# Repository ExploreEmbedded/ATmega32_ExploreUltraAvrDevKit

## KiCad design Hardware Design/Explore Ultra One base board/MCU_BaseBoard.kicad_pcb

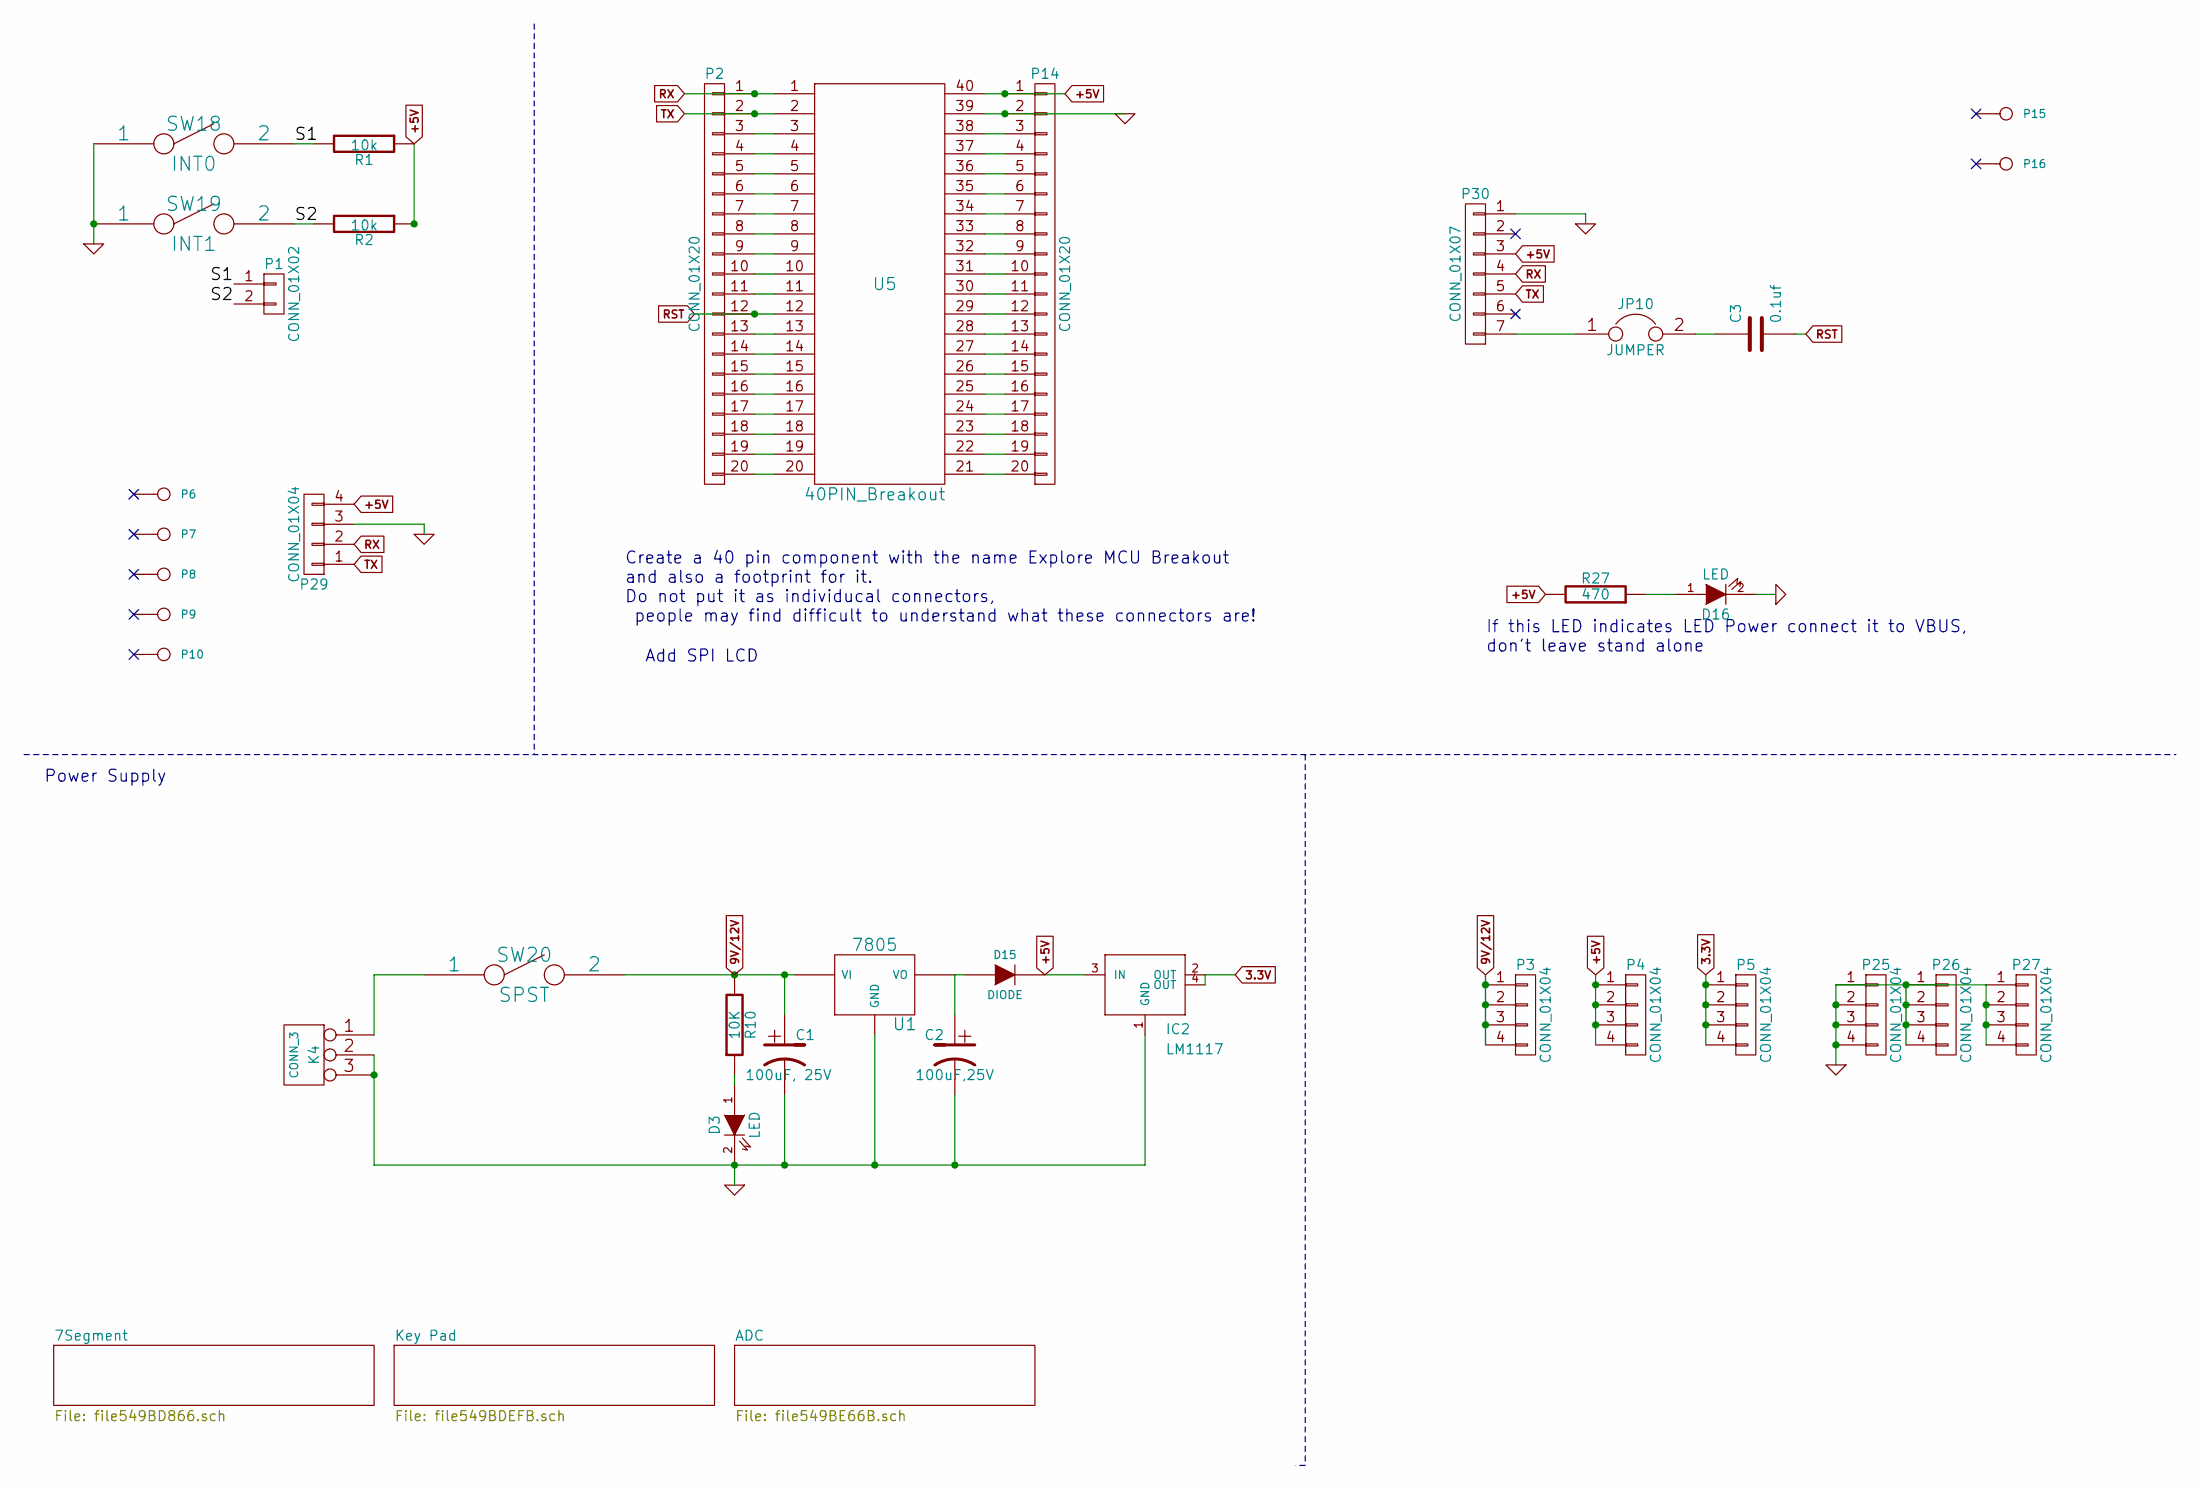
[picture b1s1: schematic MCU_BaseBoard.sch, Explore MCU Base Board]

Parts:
C1: 100uF, 25V
C2: 100uF,25V
C3: 0.1uf
D3, D16: LED
D15: DIODE
IC2: LM1117
JP10: JUMPER
K4: CONN_3
P1: CONN_01X02
P2, P14: CONN_01X20
P3, P4, P5, P25, P26, P27, P29: CONN_01X04
P6, P7, P8, P9, P10, P15, P16: CONN_1
P30: CONN_01X07
R1, R2: 10k
R10: 10K
R27: 470
SW18: INT0
SW19: INT1
SW20: SPST
U1: 7805
U5: 40PIN_Breakout

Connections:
3.3V: IC2.2 (OUT), IC2.4 (OUT), P5.1, P5.2, P5.3, P5.4; also elsewhere on the board
9V/12V: C1.1, P3.1, P3.2, P3.3, P3.4, R10.2, SW20.2, U1.VI; also elsewhere on the board
+5V: D15.2 (K), IC2.3 (IN), P4.1, P4.2, P4.3, P4.4, P14.1, P29.4, P30.3, R1.1, R2.1, R27.2, U5.40; also elsewhere on the board
/S1: P1.1, R1.2, SW18.2
/S2: P1.2, R2.2, SW19.2
GND: C1.2, C2.2, D3.2 (K), D16.2 (K), IC2.1 (GND), K4.2 (PM), K4.3, P14.2, P25.1, P25.2, P25.3, P25.4, P26.1, P26.2, P26.3, P26.4, P27.1, P27.2, P27.3, P27.4, P29.3, P30.1, SW18.1, SW19.1, U1.GND, U5.39; also elsewhere on the board
unnamed: C2.1, D15.1 (A), U1.VO
unnamed: C3.1, JP10.2
unnamed: D3.1 (A), R10.1
unnamed: D16.1 (A), R27.1
unnamed: JP10.1, P30.7
unnamed: K4.1, SW20.1
unnamed: P2.3, U5.3
unnamed: P2.4, U5.4
unnamed: P2.5, U5.5
unnamed: P2.6, U5.6
unnamed: P2.7, U5.7
unnamed: P2.8, U5.8
unnamed: P2.9, U5.9
unnamed: P2.10, U5.10
unnamed: P2.11, U5.11
unnamed: P2.13, U5.13
unnamed: P2.14, U5.14
unnamed: P2.15, U5.15
unnamed: P2.16, U5.16
unnamed: P2.17, U5.17
unnamed: P2.18, U5.18
unnamed: P2.19, U5.19
unnamed: P2.20, U5.20
unnamed: P14.3, U5.38
unnamed: P14.4, U5.37
unnamed: P14.5, U5.36
unnamed: P14.6, U5.35
unnamed: P14.7, U5.34
unnamed: P14.8, U5.33
unnamed: P14.9, U5.32
unnamed: P14.10, U5.31
unnamed: P14.11, U5.30
unnamed: P14.12, U5.29
unnamed: P14.13, U5.28
unnamed: P14.14, U5.27
unnamed: P14.15, U5.26
unnamed: P14.16, U5.25
unnamed: P14.17, U5.24
unnamed: P14.18, U5.23
unnamed: P14.19, U5.22
unnamed: P14.20, U5.21
RST: C3.2, P2.12, U5.12
RX: P2.1, P29.2, P30.4, U5.1
TX: P2.2, P29.1, P30.5, U5.2

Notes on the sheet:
Power Supply
Create a 40 pin component with the name Explore MCU Breakout and also a footprint for it. Do not put it as individucal connectors, people may find difficult to understand what these connectors are!
If this LED indicates LED Power connect it to VBUS, don't leave stand alone
Add SPI LCD

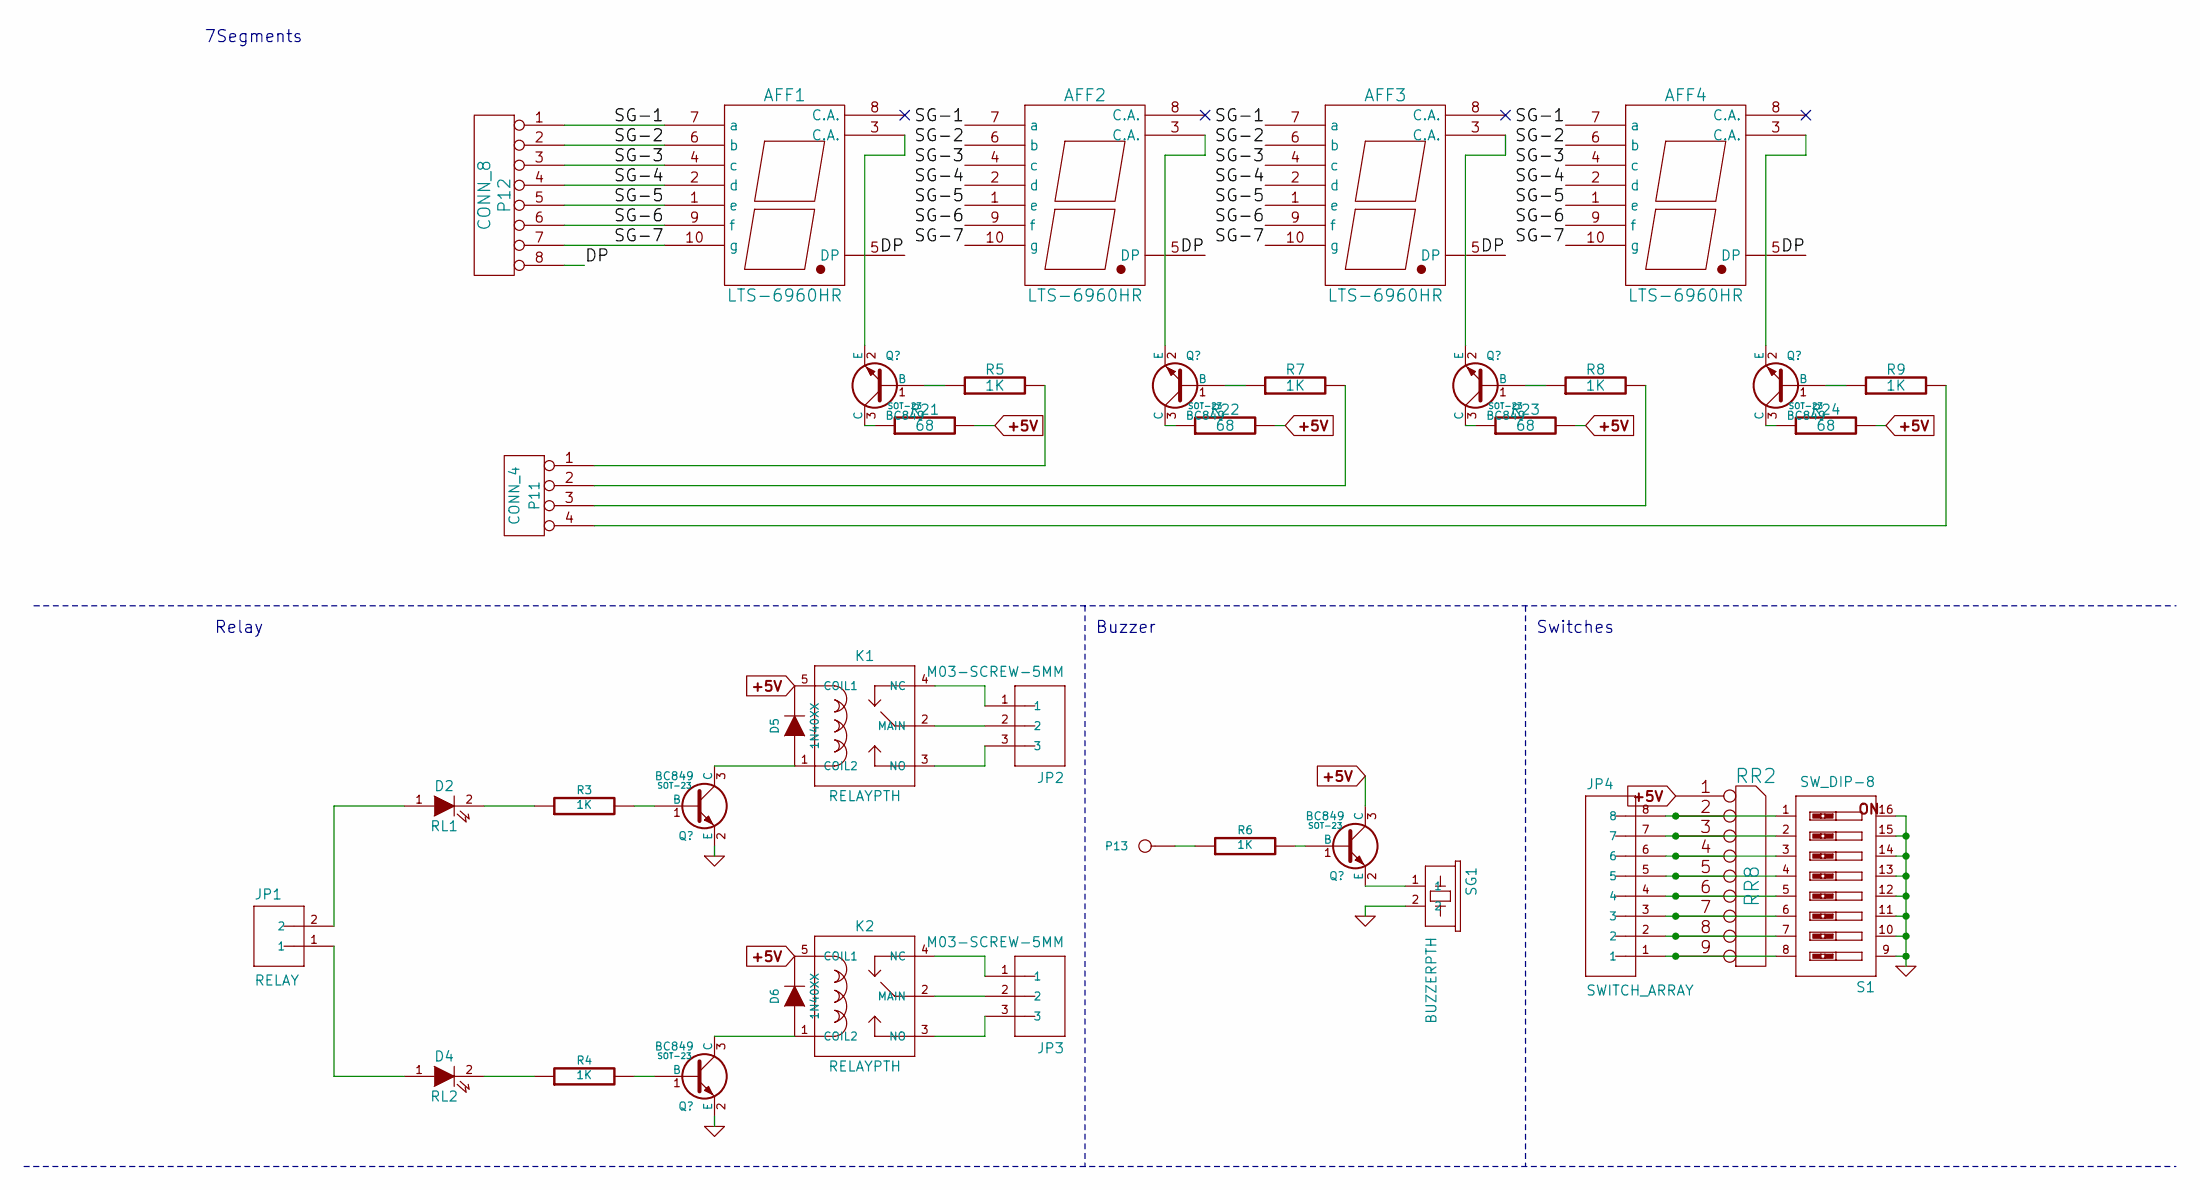
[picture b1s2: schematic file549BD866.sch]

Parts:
AFF1, AFF2, AFF3, AFF4: LTS-6960HR
D2: RL1
D4: RL2
D5, D6: 1N40XX
JP1: RELAY; SparkFun-JST-2-PTH-NS
JP2, JP3: M03-SCREW-5MM; SparkFun-SCREWTERMINAL-5MM-3
JP4: SWITCH_ARRAY; SparkFun-1X08_LOCK
K1, K2: RELAYPTH
P11: CONN_4
P12: CONN_8
P13: CONN_1
R3, R4, R6: 1K
R5, R7, R8, R9: 1K
R21, R22, R23, R24: 68
RR2: RR8
S1: SW_DIP-8; SparkFun-DIPSWITCH-08
SG1: BUZZERPTH; SparkFun-BUZZER-12MM

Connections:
+5V: D5.2 (K), D6.2 (K), K1.5 (COIL1), K2.5 (COIL1), R21.2, R22.2, R23.2, R24.2, RR2.1 (COM); also elsewhere on the board
/7Segment/DP: AFF1.5 (DP), AFF2.5 (DP), AFF3.5 (DP), AFF4.5 (DP), P12.8
/7Segment/SG-1: AFF1.7 (a), AFF2.7 (a), AFF3.7 (a), AFF4.7 (a), P12.1
/7Segment/SG-2: AFF1.6 (b), AFF2.6 (b), AFF3.6 (b), AFF4.6 (b), P12.2
/7Segment/SG-3: AFF1.4 (c), AFF2.4 (c), AFF3.4 (c), AFF4.4 (c), P12.3
/7Segment/SG-4: AFF1.2 (d), AFF2.2 (d), AFF3.2 (d), AFF4.2 (d), P12.4
/7Segment/SG-5: AFF1.1 (e), AFF2.1 (e), AFF3.1 (e), AFF4.1 (e), P12.5
/7Segment/SG-6: AFF1.9 (f), AFF2.9 (f), AFF3.9 (f), AFF4.9 (f), P12.6
/7Segment/SG-7: AFF1.10 (g), AFF2.10 (g), AFF3.10 (g), AFF4.10 (g), P12.7
GND: S1.9, S1.10, S1.11, S1.12, S1.13, S1.14, S1.15, S1.16, SG1.2; also elsewhere on the board
unnamed 46: AFF1.3 (C.A.); also elsewhere on the board
unnamed 48: AFF2.3 (C.A.); also elsewhere on the board
unnamed 50: AFF3.3 (C.A.); also elsewhere on the board
unnamed 52: AFF4.3 (C.A.); also elsewhere on the board
unnamed: D2.1 (A), JP1.2
unnamed: D2.2 (K), R3.1
unnamed: D4.1 (A), JP1.1
unnamed: D4.2 (K), R4.1
unnamed 61: D5.1 (A), K1.1 (COIL2); also elsewhere on the board
unnamed 62: D6.1 (A), K2.1 (COIL2); also elsewhere on the board
unnamed: JP2.1, K1.4 (NC)
unnamed: JP2.2, K1.2 (MAIN)
unnamed: JP2.3, K1.3 (NO)
unnamed: JP3.1, K2.4 (NC)
unnamed: JP3.2, K2.2 (MAIN)
unnamed: JP3.3, K2.3 (NO)
unnamed: JP4.1, RR2.9, S1.8
unnamed: JP4.2, RR2.8, S1.7
unnamed: JP4.3, RR2.7, S1.6
unnamed: JP4.4, RR2.6, S1.5
unnamed: JP4.5, RR2.5, S1.4
unnamed: JP4.6, RR2.4, S1.3
unnamed: JP4.7, RR2.3, S1.2
unnamed: JP4.8, RR2.2, S1.1
unnamed: P11.1, R5.2
unnamed: P11.2, R7.2
unnamed: P11.3, R8.2
unnamed: P11.4, R9.2
unnamed: P13.1, R6.1
unnamed 157: R3.2; also elsewhere on the board
unnamed 158: R4.2; also elsewhere on the board
unnamed 159: R5.1; also elsewhere on the board
unnamed 160: R21.1; also elsewhere on the board
unnamed 161: R7.1; also elsewhere on the board
unnamed 162: R22.1; also elsewhere on the board
unnamed 163: R6.2; also elsewhere on the board
unnamed 164: SG1.1; also elsewhere on the board
unnamed 165: R8.1; also elsewhere on the board
unnamed 166: R23.1; also elsewhere on the board
unnamed 167: R9.1; also elsewhere on the board
unnamed 168: R24.1; also elsewhere on the board

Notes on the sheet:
7Segments
Relay
Buzzer
Switches

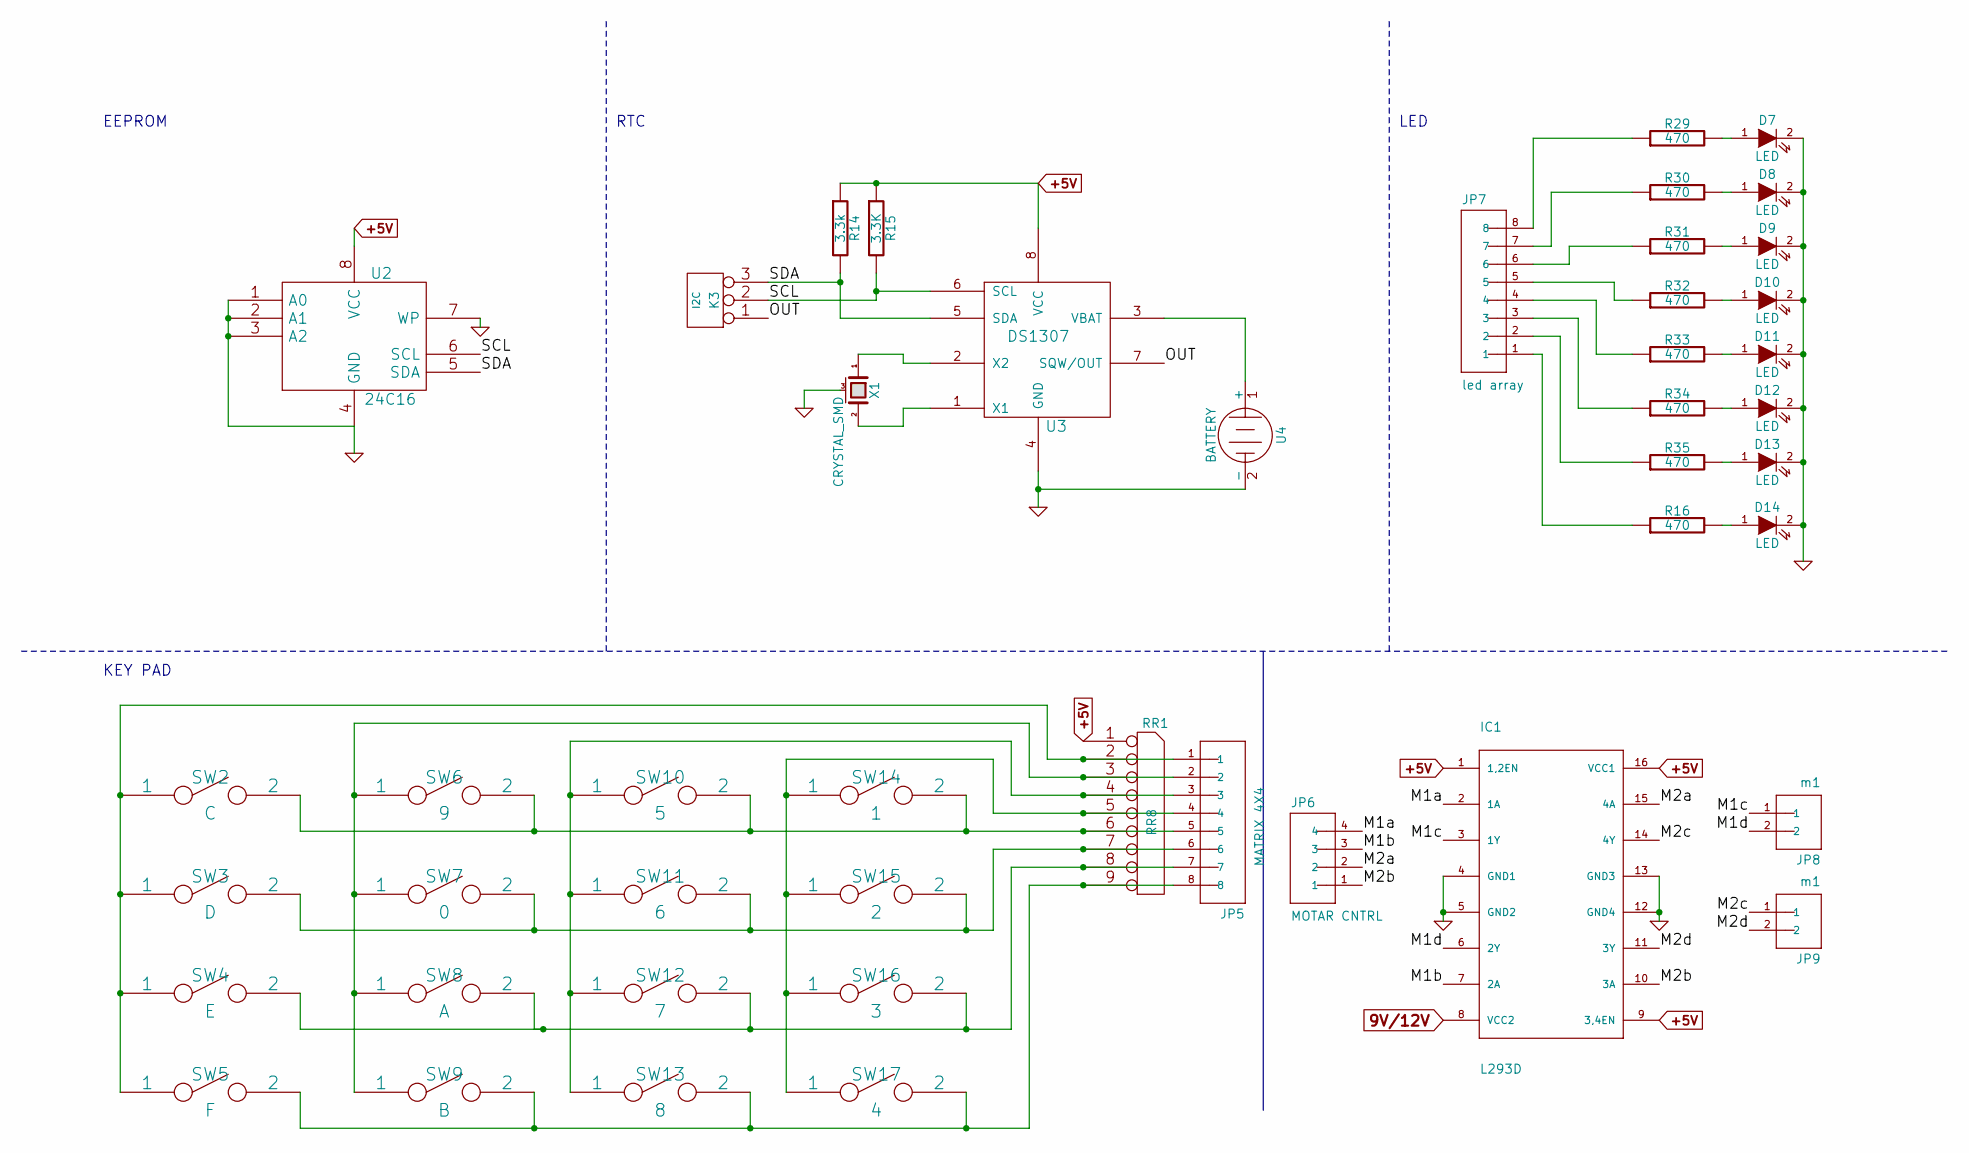
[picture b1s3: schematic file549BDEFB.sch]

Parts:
D7, D8, D9, D10, D11, D12, D13, D14: LED
IC1: L293D; sgs-thom-DIL16
JP5: MATRIX 4X4; SparkFun-1X08_LOCK
JP6: MOTAR CNTRL; SparkFun-JST-4-PTH
JP7: led array; SparkFun-1X08_LOCK
JP8, JP9: m1; SparkFun-JST-2-PTH-NS
K3: I2C
R14: 3.3k
R15: 3.3K
R16, R29, R30, R31, R32, R33, R34, R35: 470
RR1: RR8
SW2: C
SW3: D
SW4: E
SW5: F
SW6: 9
SW7: 0
SW8: A
SW9: B
SW10: 5
SW11: 6
SW12: 7
SW13: 8
SW14: 1
SW15: 2
SW16: 3
SW17: 4
U2: 24C16
U3: DS1307
U4: BATTERY
X1: CRYSTAL_SMD

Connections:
9V/12V: IC1.8 (VCC2); also elsewhere on the board
+5V: IC1.1 (1,2EN), IC1.9 (3,4EN), IC1.16 (VCC1), R14.1, R15.1, RR1.1 (COM), U2.8 (VCC), U3.8 (VCC); also elsewhere on the board
/Key Pad/M1a: IC1.2 (1A), JP6.4
/Key Pad/M1b: IC1.7 (2A), JP6.3
/Key Pad/M1c: IC1.3 (1Y), JP8.1
/Key Pad/M1d: IC1.6 (2Y), JP8.2
/Key Pad/M2a: IC1.15 (4A), JP6.2
/Key Pad/M2b: IC1.10 (3A), JP6.1
/Key Pad/M2c: IC1.14 (4Y), JP9.1
/Key Pad/M2d: IC1.11 (3Y), JP9.2
/Key Pad/OUT: K3.1, U3.7 (SQW/OUT)
/Key Pad/SCL: K3.2 (PM), R15.2, U2.6 (SCL), U3.6 (SCL)
/Key Pad/SDA: K3.3, R14.2, U2.5 (SDA), U3.5 (SDA)
GND: D7.2 (K), D8.2 (K), D9.2 (K), D10.2 (K), D11.2 (K), D12.2 (K), D13.2 (K), D14.2 (K), IC1.4 (GND1), IC1.5 (GND2), IC1.12 (GND4), IC1.13 (GND3), U2.1 (A0), U2.2 (A1), U2.3 (A2), U2.4 (GND), U2.7 (WP), U3.4 (GND), U4.2 (-), X1.3 (case); also elsewhere on the board
unnamed: D7.1 (A), R29.2
unnamed: D8.1 (A), R30.2
unnamed: D9.1 (A), R31.2
unnamed: D10.1 (A), R32.2
unnamed: D11.1 (A), R33.2
unnamed: D12.1 (A), R34.2
unnamed: D13.1 (A), R35.2
unnamed: D14.1 (A), R16.2
unnamed: JP5.1, RR1.2, SW2.1, SW3.1, SW4.1, SW5.1
unnamed: JP5.2, RR1.3, SW6.1, SW7.1, SW8.1, SW9.1
unnamed: JP5.3, RR1.4, SW10.1, SW11.1, SW12.1, SW13.1
unnamed: JP5.4, RR1.5, SW14.1, SW15.1, SW16.1, SW17.1
unnamed: JP5.5, RR1.6, SW2.2, SW6.2, SW10.2, SW14.2
unnamed: JP5.6, RR1.7, SW3.2, SW7.2, SW11.2, SW15.2
unnamed: JP5.7, RR1.8, SW4.2, SW8.2, SW12.2, SW16.2
unnamed: JP5.8, RR1.9, SW5.2, SW9.2, SW13.2, SW17.2
unnamed: JP7.1, R16.1
unnamed: JP7.2, R35.1
unnamed: JP7.3, R34.1
unnamed: JP7.4, R33.1
unnamed: JP7.5, R32.1
unnamed: JP7.6, R31.1
unnamed: JP7.7, R30.1
unnamed: JP7.8, R29.1
unnamed: U3.1 (X1), X1.2
unnamed: U3.2 (X2), X1.1
unnamed: U3.3 (VBAT), U4.1 (+)

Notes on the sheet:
EEPROM
RTC
LED
KEY PAD

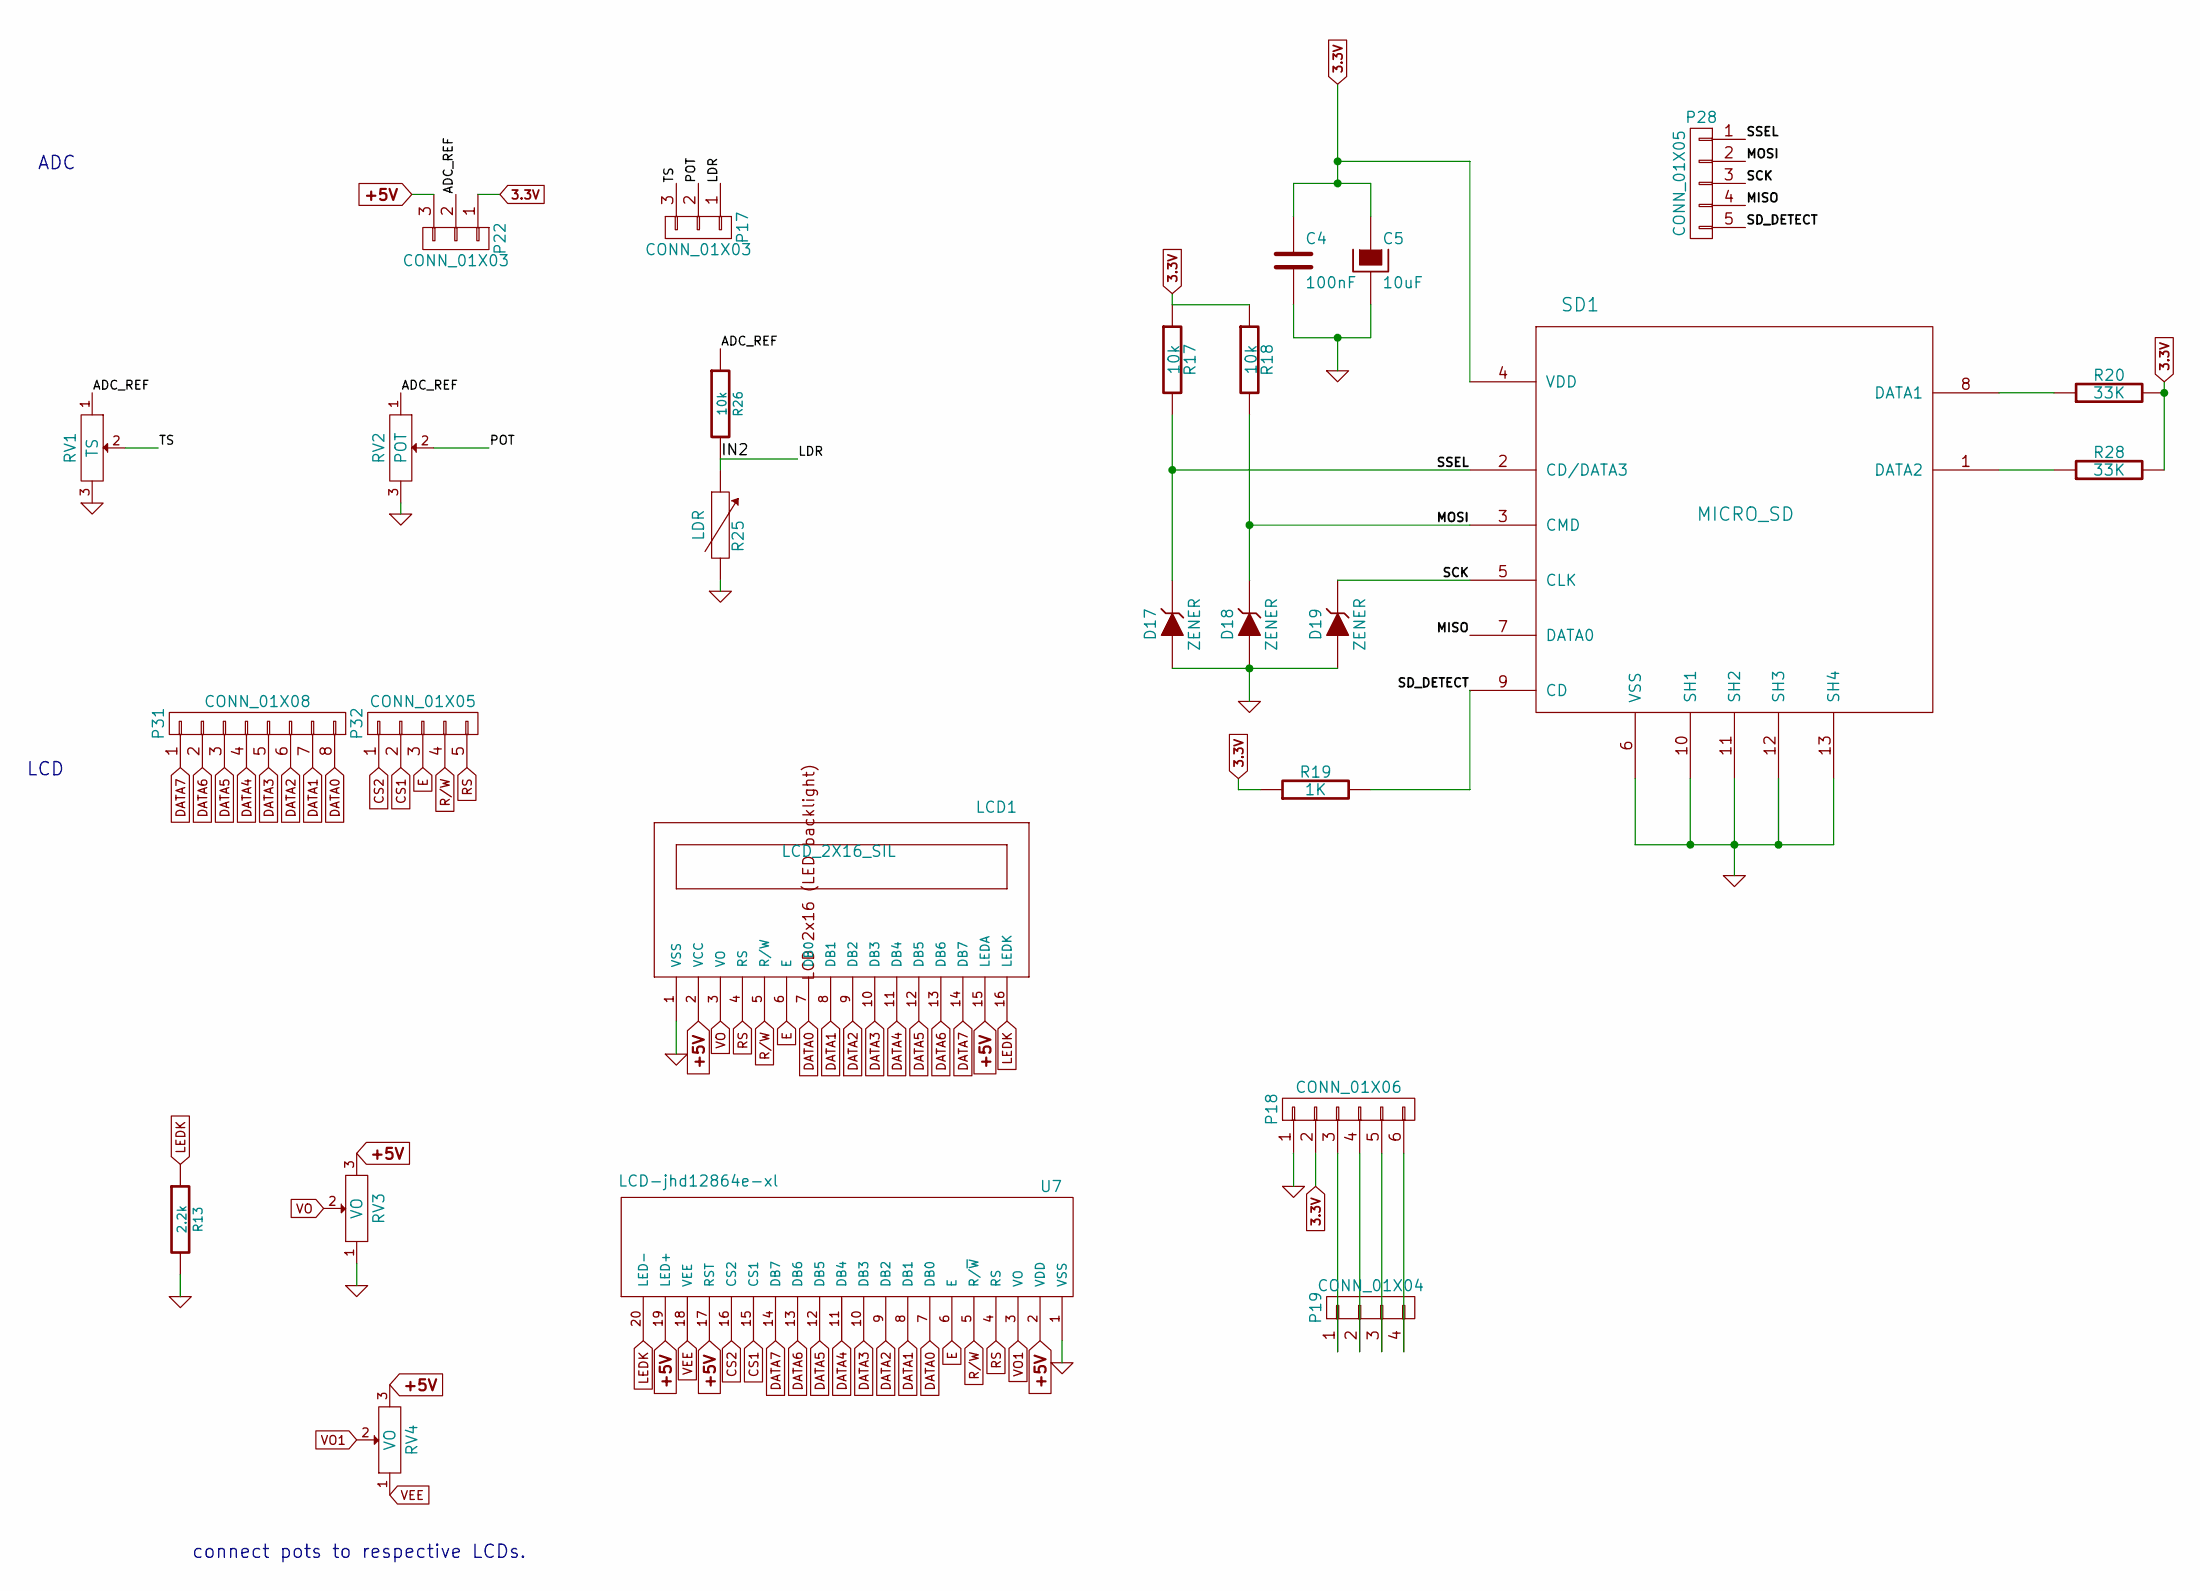
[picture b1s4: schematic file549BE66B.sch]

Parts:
C4: 100nF
C5: 10uF
D17, D18, D19: ZENER
LCD1: LCD_2X16_SIL; lcd_2x16_led_backlight-HY-1602F
P17, P22: CONN_01X03
P18: CONN_01X06
P19: CONN_01X04
P28, P32: CONN_01X05
P31: CONN_01X08
R13: 2.2k
R17, R18: 10k
R19: 1K
R20, R28: 33K
R25: LDR
R26: 10k
RV1: TS
RV2: POT
RV3, RV4: VO
SD1: MICRO_SD
U7: LCD-jhd12864e-xl

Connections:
3.3V: C4.1, C5.1, P18.2, P22.1, R17.1, R18.1, R19.1, R20.2, R28.2, SD1.4 (VDD); also elsewhere on the board
+5V: LCD1.2 (VCC), LCD1.15 (LEDA), P22.3, RV3.3, RV4.3, U7.2 (VDD), U7.17 (RST), U7.19 (LED+); also elsewhere on the board
/ADC/ADC_REF: P22.2, R26.1, RV1.1, RV2.1
/ADC/IN2: P17.1, R25.1, R26.2
/ADC/MISO: P28.4, SD1.7 (DATA0)
/ADC/MOSI: D18.2 (K), P28.2, R18.2, SD1.3 (CMD)
/ADC/POT: P17.2, RV2.2
/ADC/SCK: D19.2 (K), P28.3, SD1.5 (CLK)
/ADC/SD_DETECT: P28.5, R19.2, SD1.9 (CD)
/ADC/SSEL: D17.2 (K), P28.1, R17.2, SD1.2 (CD/DATA3)
/ADC/TS: P17.3, RV1.2
CS1: P32.2, U7.15 (CS1)
CS2: P32.1, U7.16 (CS2)
DATA0: LCD1.7 (DB0), P31.8, U7.7 (DB0)
DATA1: LCD1.8 (DB1), P31.7, U7.8 (DB1)
DATA2: LCD1.9 (DB2), P31.6, U7.9 (DB2)
DATA3: LCD1.10 (DB3), P31.5, U7.10 (DB3)
DATA4: LCD1.11 (DB4), P31.4, U7.11 (DB4)
DATA5: LCD1.12 (DB5), P31.3, U7.12 (DB5)
DATA6: LCD1.13 (DB6), P31.2, U7.13 (DB6)
DATA7: LCD1.14 (DB7), P31.1, U7.14 (DB7)
E: LCD1.6 (E), P32.3, U7.6 (E)
GND: C4.2, C5.2, D17.1 (A), D18.1 (A), D19.1 (A), LCD1.1 (VSS), P18.1, R13.2, R25.2, RV1.3, RV2.3, RV3.1, SD1.6 (VSS), SD1.10 (SH1), SD1.11 (SH2), SD1.12 (SH3), SD1.13 (SH4), U7.1 (VSS); also elsewhere on the board
LEDK: LCD1.16 (LEDK), R13.1, U7.20 (LED-)
unnamed: P18.3, P19.1
unnamed: P18.4, P19.2
unnamed: P18.5, P19.3
unnamed: P18.6, P19.4
unnamed: R20.1, SD1.8 (DATA1)
unnamed: R28.1, SD1.1 (DATA2)
R/W: LCD1.5 (R/W), P32.4, U7.5 (R/~W)
RS: LCD1.4 (RS), P32.5, U7.4 (RS)
VEE: RV4.1, U7.18 (VEE)
VO: LCD1.3 (VO), RV3.2
VO1: RV4.2, U7.3 (VO)

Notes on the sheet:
ADC
LCD
connect pots to respective LCDs.

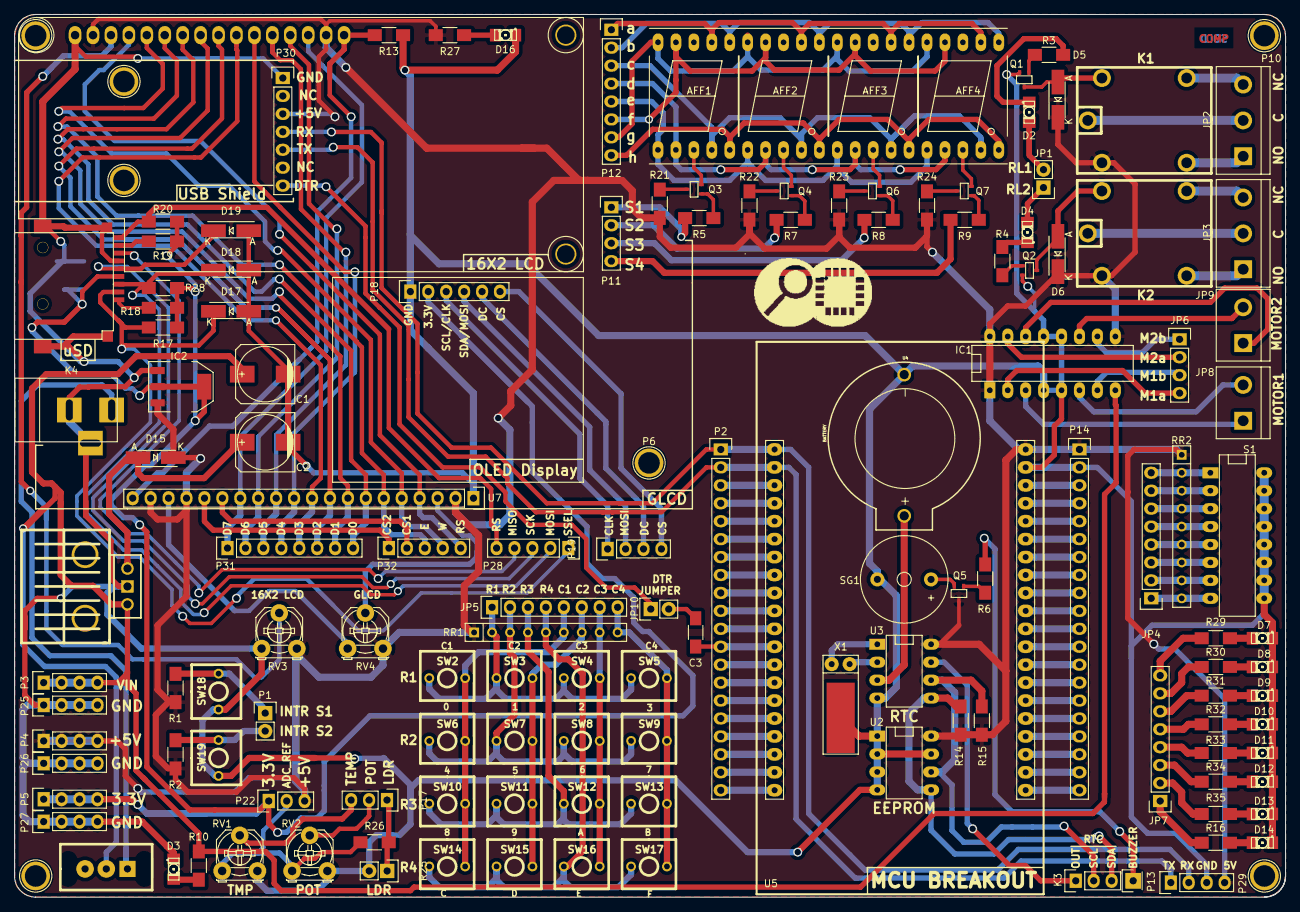
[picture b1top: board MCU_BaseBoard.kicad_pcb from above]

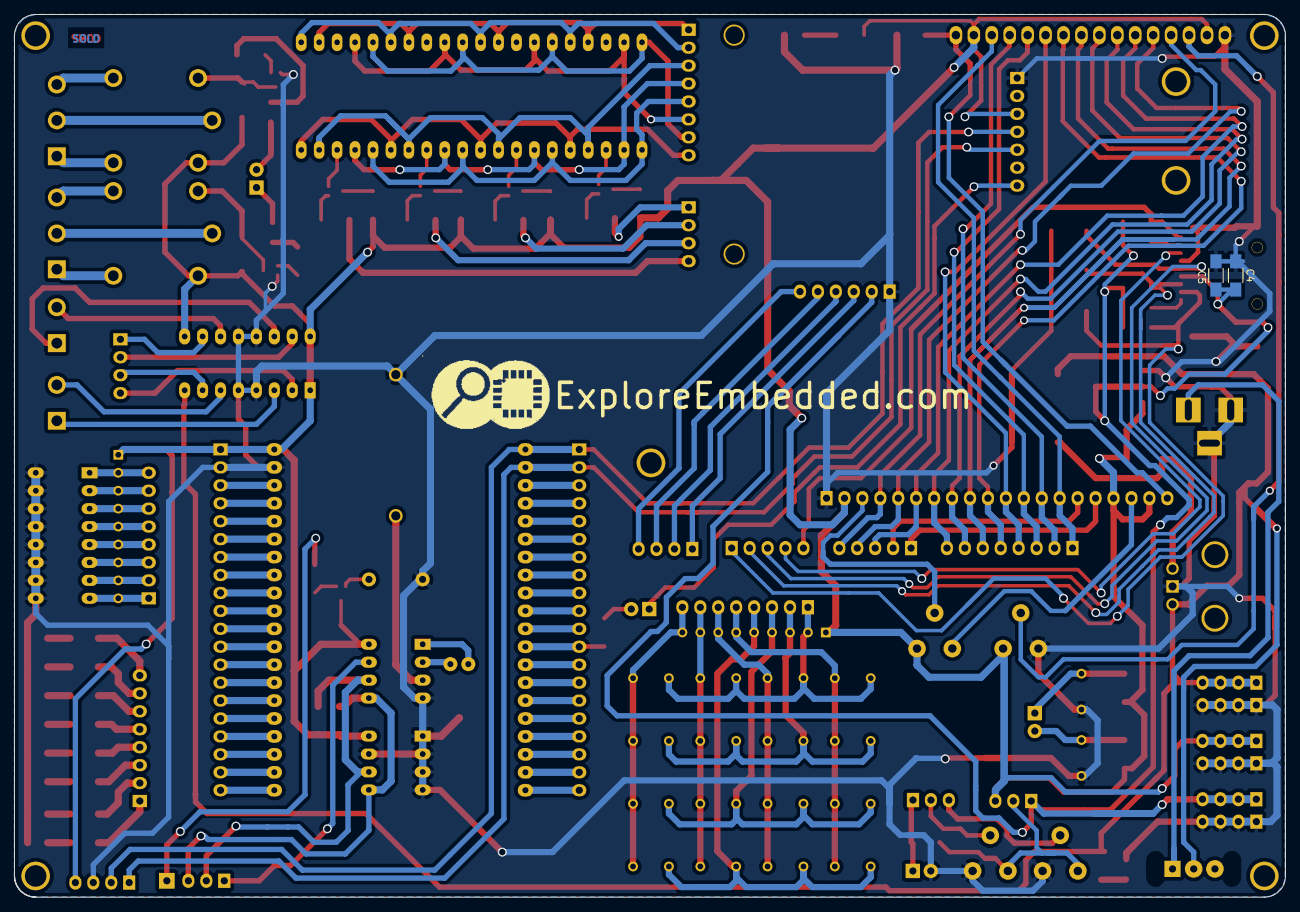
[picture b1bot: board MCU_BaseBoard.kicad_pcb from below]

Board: 2 copper layers, 180.0 x 125.0 mm, 149 parts (3 on the bottom side), 169 nets.

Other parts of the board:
EE_LOGO: EE_LOGO(2)
EE_LOGO#2: EE_LOGO(2)
Q1, Q2, Q3, Q4, Q5, Q6, Q7: BC849; sc70

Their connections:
+5V: Q5.3; also elsewhere on the board
GND: Q1.2, Q2.2; also elsewhere on the board
unnamed 46: Q3.2; also elsewhere on the board
unnamed 48: Q4.2; also elsewhere on the board
unnamed 50: Q6.2; also elsewhere on the board
unnamed 52: Q7.2; also elsewhere on the board
unnamed 61: Q1.3; also elsewhere on the board
unnamed 62: Q2.3; also elsewhere on the board
unnamed 157: Q1.1; also elsewhere on the board
unnamed 158: Q2.1; also elsewhere on the board
unnamed 159: Q3.1; also elsewhere on the board
unnamed 160: Q3.3; also elsewhere on the board
unnamed 161: Q4.1; also elsewhere on the board
unnamed 162: Q4.3; also elsewhere on the board
unnamed 163: Q5.1; also elsewhere on the board
unnamed 164: Q5.2; also elsewhere on the board
unnamed 165: Q6.1; also elsewhere on the board
unnamed 166: Q6.3; also elsewhere on the board
unnamed 167: Q7.1; also elsewhere on the board
unnamed 168: Q7.3; also elsewhere on the board

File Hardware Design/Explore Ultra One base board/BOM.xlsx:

Id | Designator | Package | Quantity | Designation | 50 quantity | Price | Vendor
1 | SW20 | SPSPT_XL | 1 | SPST | 50
2 | LCD1 | WC1602A | 1 | LCD_2X16_SIL | 50
3 | C1,C2 | c_elec_8x10.5 | 2 | 100uF, 25V | 100
4 | C3 | C_1206_HandSoldering | 1 | 0.1uf | 50
5 | C4 | C_1206_HandSoldering | 1 | 100nF | 50
6 | C5 | C_1206_HandSoldering | 1 | 10uF | 50
7 | D2 | LED-1206 RED | 1 | RL1 | 50
8 | D3,D7,D8,D9,D10,D11,D12,D13,D14,D16 | LED-1206 GREEN | 10 | LED | 500
9 | D4 | LED-1206 GREEN | 1 | RL2 | 50
10 | D5,D6 | Diode-SMA_Handsoldering | 2 | 1N4007 SOD80 | 100
11 | D15 | Diode-SMA_Handsoldering | 1 | 1N4007 SOD80 | 50
12 | D17,D18,D19 | Diode-SMA_Handsoldering | 3 | ZENER 3.3V SOD80 | 150
13 | IC1 | DIP-16__300_ELL | 1 | L293D | 50
14 | IC2 | SOT-223 | 1 | LM1117(3V3) | 50
15 | JP2,JP3 | bornier3 3PIN | 2 | MKDSN | 100
16 | JP4 | Pin_Header_Straight_1x08 | 1 | SWITCH_ARRAY | 50 | 4 stick male
17 | JP5 | Pin_Header_Straight_1x08 | 1 | MATRIX 4X4 | 50 | 2 stick Female
18 | JP6 | Pin_Header_Straight_1x04 | 1 | MOTAR CNTRL | 50 | 1 stick Female R/A
19 | JP7 | Pin_Header_Straight_1x08 | 1 | led array | 50 | 1 stick male long
20 | JP8,JP9 | bornier2 2PIN | 2 | MKDSN | 100
21 | K3 | Pin_Header_Straight_1x03 | 1 | I2C | 50
22 | K4 | BARREL_JACK | 1 | CONN_3 | 50
23 | P3,P4,P5,P25,P26,P27,P29,P17 | Pin_Header_Straight_1x04 | 8 | CONN_01X04 | 400
25 | P11 | Pin_Header_Straight_1x04 | 1 | CONN_4 | 50
26 | P12 | Pin_Header_Straight_1x08 | 1 | CONN_8 | 50
27 | P13 | Pin_Header_Straight_1x01 | 1 | CONN_1 | 50
28 | P22,P15 | Pin_Header_Straight_1x03 | 2 | CONN_01X03 | 100
29 | P28,P32 | Pin_Header_Straight_1x05 | 2 | CONN_01X05 | 100
30 | Q2,Q3,Q4,Q5,Q6,Q7,Q1 | SMD BC847 | 7 | BC847 SMD | 350
31 | R1,R2,R17,R18,R26 | R_1206_HandSoldering | 5 | 10k | 250
32 | R3,R4,R5,R6,R7,R8,R9,R19 | R_1206_HandSoldering | 8 | 1K | 400
33 | R10 | R_1206_HandSoldering | 1 | 10K | 50
34 | R13 | R_1206_HandSoldering | 1 | 2.2k | 50
35 | R14 | R_1206_HandSoldering | 1 | 3.3k | 50
36 | R15 | R_1206_HandSoldering | 1 | 3.3K | 50
37 | R16,R27,R29,R30,R31,R32,R33,R34,R35 | R_1206_HandSoldering | 9 | 470 | 450
38 | R20,R28 | R_1206_HandSoldering | 2 | 33K | 100
39 | R21,R22,R23,R24 | R_1206_HandSoldering | 4 | 68 | 200
40 | RR1,RR2 | Pull uP array 10k | 2 | RR8 | 100
41 | RV1 | LM35 | 1 | TS | 50
42 | RV2 | Potentiometer_Triwood_RM-065 | 1 | POT | 50
43 | RV3,RV4 | Potentiometer_Triwood_RM-065 | 2 | VO | 100
44 | S1 | DIP-16__300_ELL | 1 | SW_DIP-8 | 50
45 | SD1 | Micro_SD | 1 | MICRO_SD | 50
46 | SG1 | Buzzer_12x9.5RM7.6 | 1 | BUZZERPTH | 50
47 | SW2 | SW_PUSH_SMALL_2pin_3D_xl | 1 | C | 50
48 | SW3 | SW_PUSH_SMALL_2pin_3D_xl | 1 | D | 50
49 | SW4 | SW_PUSH_SMALL_2pin_3D_xl | 1 | E | 50
50 | SW5 | SW_PUSH_SMALL_2pin_3D_xl | 1 | F | 50
51 | SW6 | SW_PUSH_SMALL_2pin_3D_xl | 1 | 9 | 50
52 | SW7 | SW_PUSH_SMALL_2pin_3D_xl | 1 | 0 | 50
53 | SW8 | SW_PUSH_SMALL_2pin_3D_xl | 1 | A | 50
54 | SW9 | SW_PUSH_SMALL_2pin_3D_xl | 1 | B | 50
55 | SW10 | SW_PUSH_SMALL_2pin_3D_xl | 1 | 5 | 50
56 | SW11 | SW_PUSH_SMALL_2pin_3D_xl | 1 | 6 | 50
57 | SW12 | SW_PUSH_SMALL_2pin_3D_xl | 1 | 7 | 50
58 | SW13 | SW_PUSH_SMALL_2pin_3D_xl | 1 | 8 | 50
59 | SW14 | SW_PUSH_SMALL_2pin_3D_xl | 1 | 1 | 50
60 | SW15 | SW_PUSH_SMALL_2pin_3D_xl | 1 | 2 | 50
61 | SW16 | SW_PUSH_SMALL_2pin_3D_xl | 1 | 3 | 50
62 | SW17 | SW_PUSH_SMALL_2pin_3D_xl | 1 | 4 | 50
63 | SW18 | SW_PUSH_SMALL_2pin_3D_xl | 1 | INT0 | 50
64 | SW19 | SW_PUSH_SMALL_2pin_3D_xl | 1 | INT1 | 50
65 | U2 | DIP-8__300_ELL and IC | 1 | 24C16 | 50
66 | U3 | DIP-8__300_ELL and IC | 1 | DS1307 | 50
67 | U4 | BATT_rtc_XL | 1 | BATTERY | 50
68 | U7 | Pin_Header_Straight_1x20 | 1 | LCD-jhd12864e-xl | 50
69 | JP1 | Pin_Header_Straight_1x02 | 1 | RELAY | 50
70 | JP10 | Pin_Header_Straight_1x02 | 1 | JUMPER | 50
71 | K1,K2 | 5V AIFU Relays | 2 | RELAYPTH | 100
72 | U1 | 1A regulator | 1 | 7805 | 50
73 | R25 | Pin_Header_Straight_1x02 | 1 | LDR | 50
74 | P30 | Pin_Header_Straight_1x07 | 1 | CONN_01X07 | 50
75 | P31 | Pin_Header_Straight_1x08 | 1 | CONN_01X08 | 50
76 | P1 | Pin_Header_Straight_1x02 | 1 | CONN_01X02 | 50
77 | AFF2,AFF3,AFF4,AFF1 | 7SegmentLED_LT542 | 4 | LT542 CA | 200
79 | P2,P14 | Pin_Header_Straight_1x20 | 2 | CONN_01X20 | 100
80 | X1 | RTC_Crystal | 1 | 32.768kHZ | 50

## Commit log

2016-03-19 code library updated
2016-03-19 fritzing diagram for interrupt
2016-03-24 Timer and Interrupt code updated
2016-04-02 Tutorial Code updated
2016-04-19 Tutorial codes updated
    Tutorial codes updated
2016-05-11 Updated the Test Code
    Updated the Test Code for ADC, SevenSegment and Eeprom
2017-03-29 Updated Ad, PWM, Timers
    Updated Ad, PWM, Timers
2017-03-29 Added Boot Loader
    Added Boot Loader
2017-04-13 Updated Fuse Bits in Readme
    Updated Fuse Bits in Readme
2017-04-13 Updated Fuse bits infor in read me
    Updated Fuse bits infor in read me
2017-04-13 Updated fuse bits info in readme
    Updated fuse bits info in readme
